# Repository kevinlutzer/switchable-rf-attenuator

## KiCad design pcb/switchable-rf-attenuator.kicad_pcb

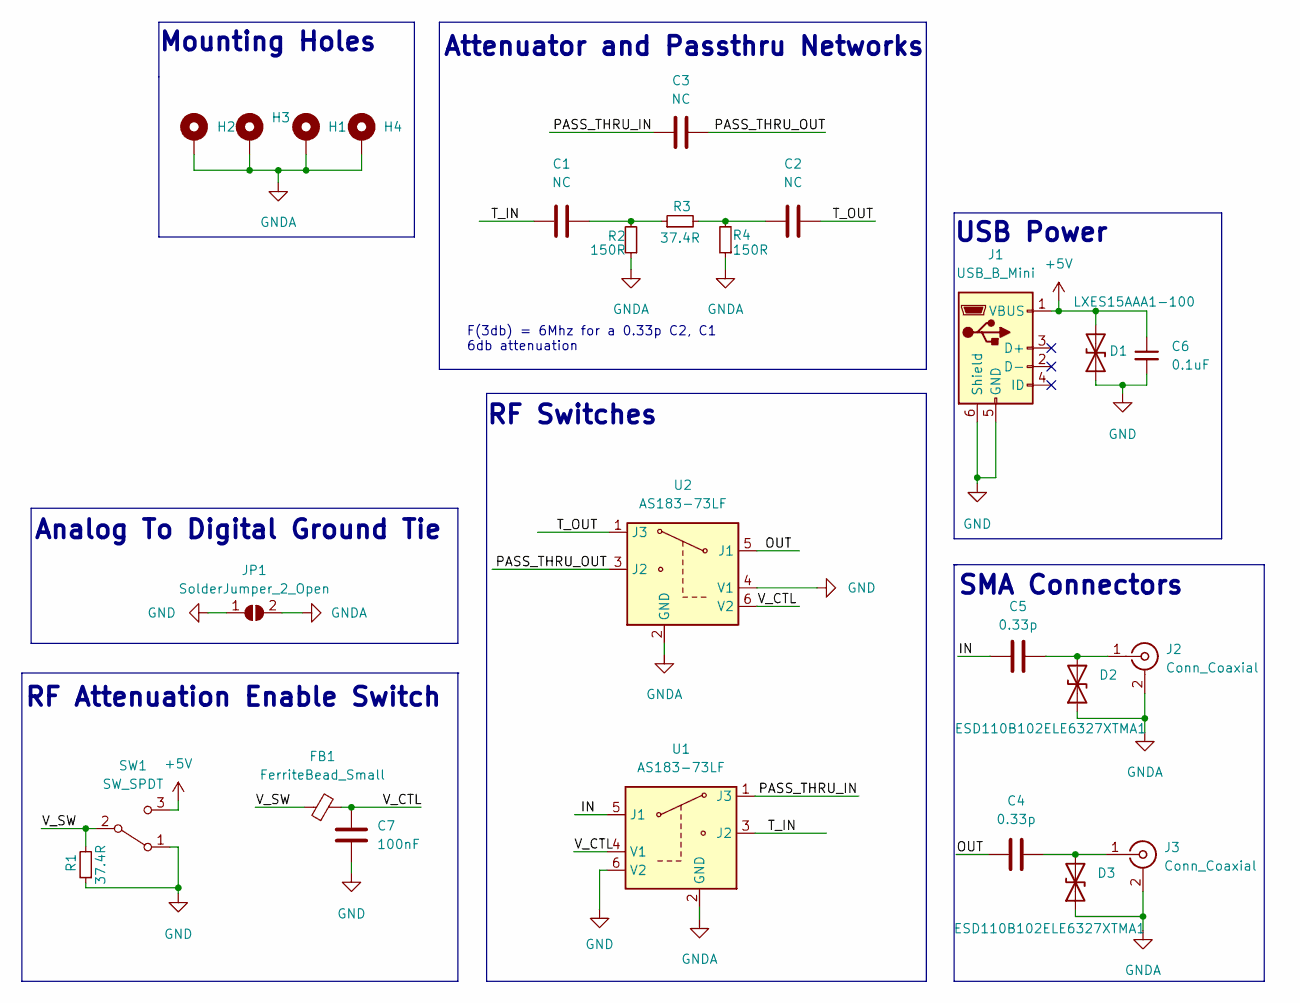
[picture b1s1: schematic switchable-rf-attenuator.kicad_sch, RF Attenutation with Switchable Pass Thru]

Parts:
C1, C2, C3: NC; C_0805_2012Metric
C4, C5: 0.33p; C_0805_2012Metric
C6: 0.1uF; C_0805_2012Metric
C7: 100nF; C_0603_1608Metric
D1: LXES15AAA1-100; D_0402_1005Metric
D2, D3: ESD110B102ELE6327XTMA1; D_0402_1005Metric
FB1: FerriteBead_Small; L_0603_1608Metric
H1, H2, H3, H4: MountingHole_Pad; MountingHole_2.2mm_M2_Pad_Via
J1: USB_B_Mini; USB_Mini-B_Wuerth_65100516121_Horizontal
J2, J3: Conn_Coaxial; SMA_Molex_73251-2120_EdgeMount_Horizontal
JP1: SolderJumper_2_Open; SolderJumper-2_P1.3mm_Open_TrianglePad1.0x1.5mm
R1, R3: 37.4R; R_0805_2012Metric
R2, R4: 150R; R_0805_2012Metric
SW1: SW_SPDT; SW_SPDT_CK-JS102011SAQN
U1, U2: AS183-73LF; SOT-363_SC-70-6

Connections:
+5V: C6.1, D1.2 (A2), J1.1 (VBUS), SW1.3 (C)
/IN: C5.1, U1.5 (J1)
/OUT: C4.1, U2.5 (J1)
/PASS_THRU_IN: C3.1, U1.1 (J3)
/PASS_THRU_OUT: C3.2, U2.3 (J2)
/T_IN: C1.1, U1.3 (J2)
/T_OUT: C2.2, U2.1 (J3)
/V_CTL: C7.1, FB1.2, U1.4 (V1), U2.6 (V2)
/V_SW: FB1.1, R1.2, SW1.2 (B)
GND: C6.2, C7.2, D1.1 (A1), J1.5 (GND), J1.6 (Shield), JP1.1 (A), R1.1, SW1.1 (A), U1.6 (V2), U2.4 (V1)
GNDA: D2.1 (A1), D3.1 (A1), H1.1, H2.1, H3.1, H4.1, J2.2 (Ext), J3.2 (Ext), JP1.2 (B), R2.1, R4.1, U1.2 (GND), U2.2 (GND)
unnamed: C1.2, R2.2, R3.1
unnamed: C2.1, R3.2, R4.2
unnamed: C4.2, D3.2 (A2), J3.1 (In)
unnamed: C5.2, D2.2 (A2), J2.1 (In)

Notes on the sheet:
SMA Connectors
Analog To Digital Ground Tie
RF Switches
USB Power
Mounting Holes
Attenuator and Passthru Networks
F(3db) = 6Mhz for a 0.33p C2, C1 6db attenuation
RF Attenuation Enable Switch

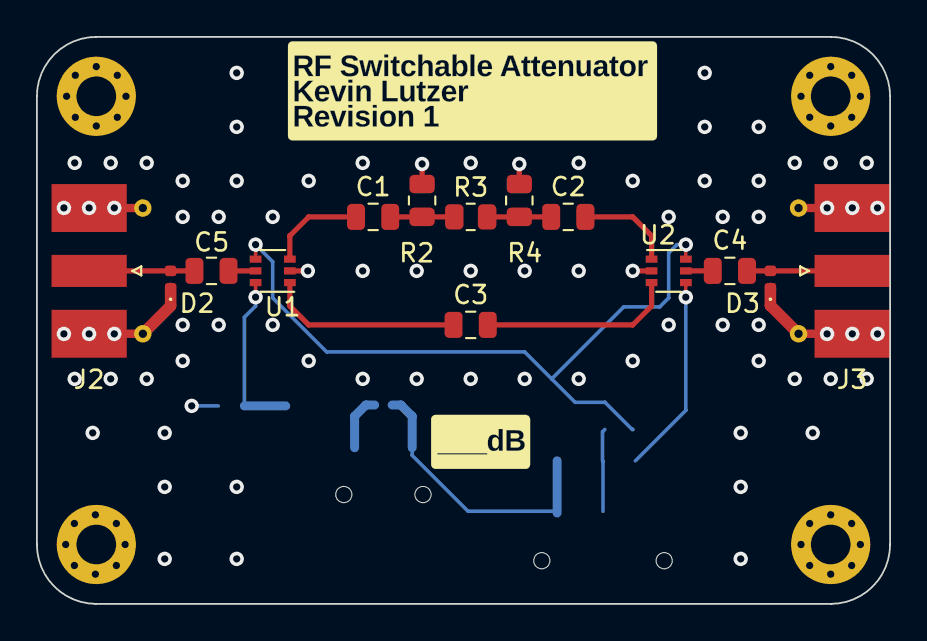
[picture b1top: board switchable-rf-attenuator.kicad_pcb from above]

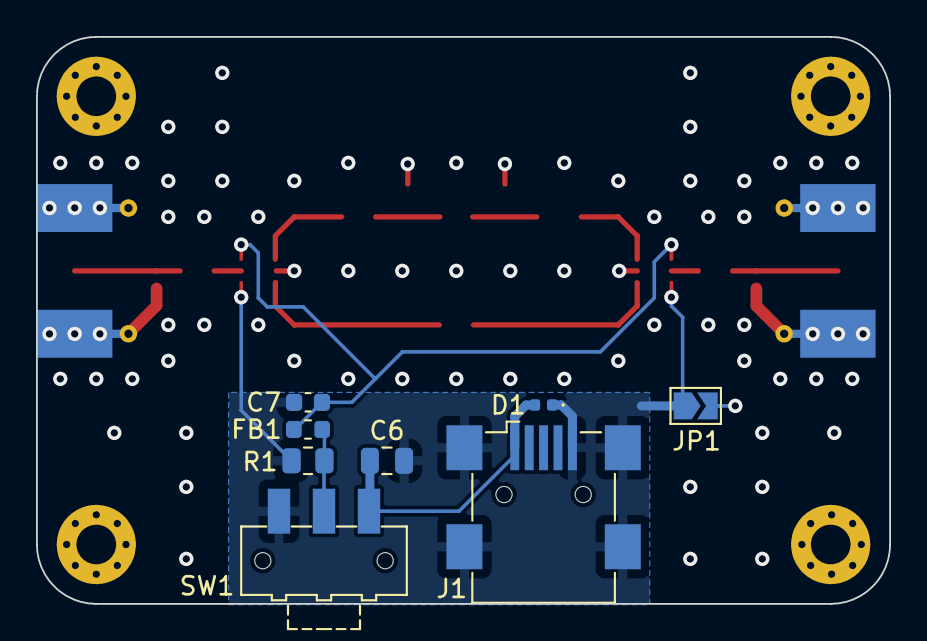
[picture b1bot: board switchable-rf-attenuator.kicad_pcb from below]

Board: 4 copper layers, 47.4 x 31.5 mm, 26 parts (8 on the bottom side), 15 nets.

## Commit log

2022-10-13 build out most of the rf attenuator, including the full schematic and board
2022-10-13 add the sim file
2022-10-13 move the sim file around
2022-10-18 finish the trace routing
2022-10-18 add a note
2022-10-18 add assets
2022-10-19 round corners, add stitching vias and via fence around tl
2022-10-19 remvoe backups and add gitignre
2022-11-15 add bom and add a LPF for the DC signals
2022-11-15 remove the backups
2022-11-15 cleanup FB1
